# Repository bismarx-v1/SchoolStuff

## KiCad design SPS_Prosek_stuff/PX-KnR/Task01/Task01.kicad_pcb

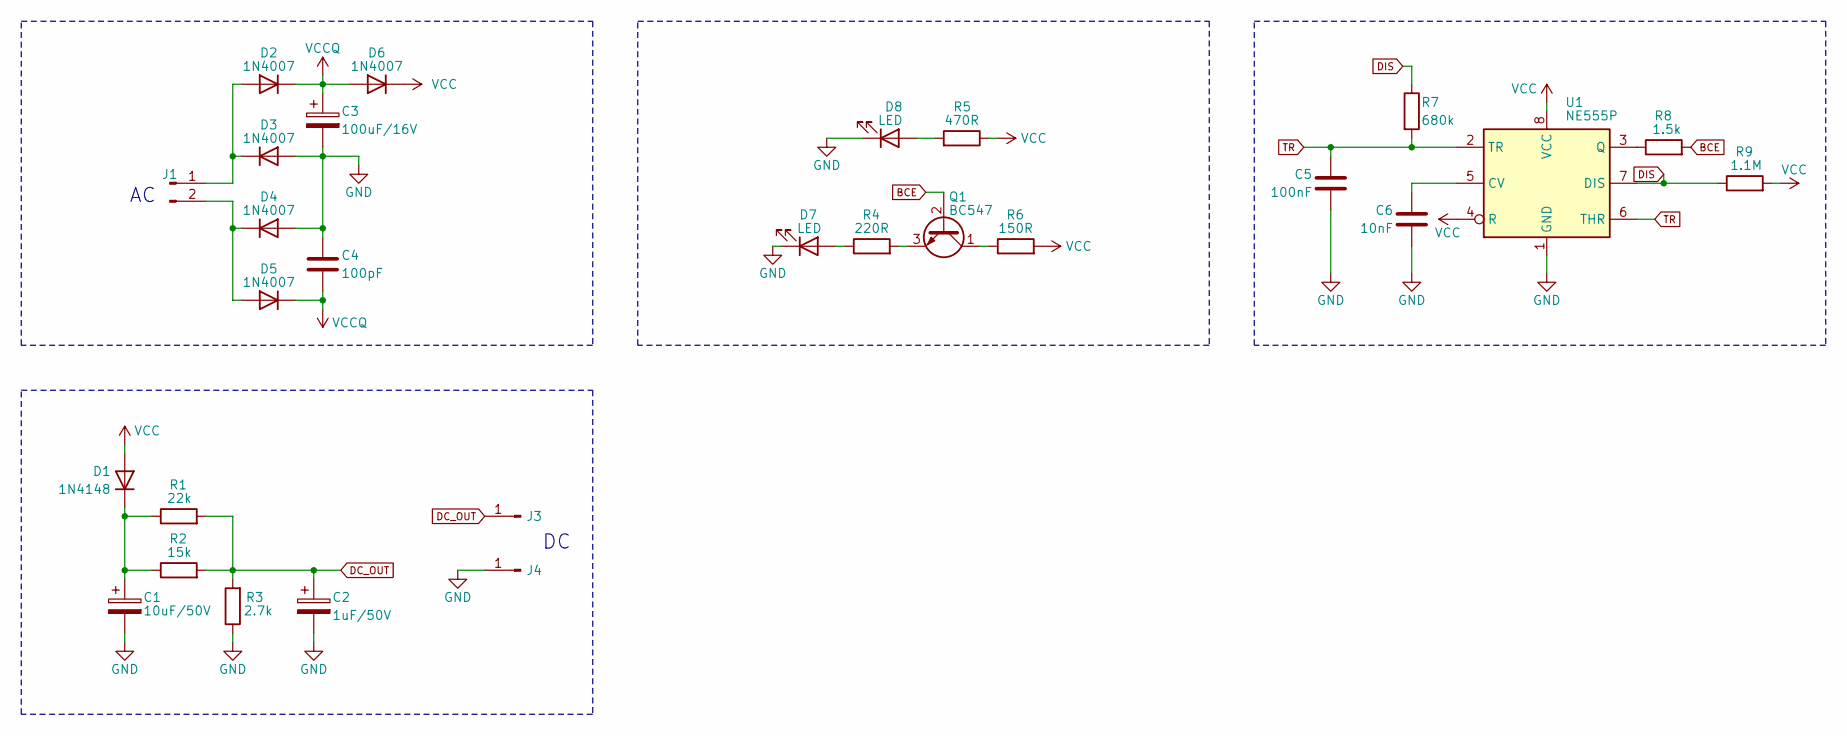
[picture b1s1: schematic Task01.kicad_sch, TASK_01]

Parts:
C1: 10uF/50V; CP_Radial_D6.3mm_P2.50mm
C2: 1uF/50V; CP_Radial_D6.3mm_P2.50mm
C3: 100uF/16V; CP_Radial_D6.3mm_P2.50mm
C4: 100pF; C_Disc_D6.0mm_W2.5mm_P5.00mm
C5: 100nF; C_Disc_D6.0mm_W2.5mm_P5.00mm
C6: 10nF; C_Disc_D6.0mm_W2.5mm_P5.00mm
D1: 1N4148; D_DO-35_SOD27_P7.62mm_Horizontal
D2, D3, D4, D5, D6: 1N4007; D_DO-41_SOD81_P10.16mm_Horizontal
D7, D8: LED; LED_D5.0mm_Clear
J1: Conn_01x02_Pin; PinHeader_1x02_P2.54mm_Vertical
J3, J4: DC; PinHeader_1x01_P2.54mm_Vertical
Q1: BC547; TO-92_Inline
R1: 22k; R_Axial_DIN0207_L6.3mm_D2.5mm_P10.16mm_Horizontal
R2: 15k; R_Axial_DIN0207_L6.3mm_D2.5mm_P10.16mm_Horizontal
R3: 2.7k; R_Axial_DIN0207_L6.3mm_D2.5mm_P10.16mm_Horizontal
R4: 220R; R_Axial_DIN0207_L6.3mm_D2.5mm_P10.16mm_Horizontal
R5: 470R; R_Axial_DIN0207_L6.3mm_D2.5mm_P10.16mm_Horizontal
R6: 150R; R_Axial_DIN0207_L6.3mm_D2.5mm_P10.16mm_Horizontal
R7: 680k; R_Axial_DIN0207_L6.3mm_D2.5mm_P10.16mm_Horizontal
R8: 1.5k; R_Axial_DIN0207_L6.3mm_D2.5mm_P10.16mm_Horizontal
R9: 1.1M; R_Axial_DIN0207_L6.3mm_D2.5mm_P10.16mm_Horizontal
U1: NE555P; DIP-8_W7.62mm

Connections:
BCE: Q1.2 (B), R8.2
DC_OUT: C2.1, J3.1, R1.2, R2.2, R3.2
DIS: R7.1, R9.1, U1.7 (DIS)
GND: C1.2, C2.2, C3.2, C4.1, C5.2, C6.2, D3.2 (A), D4.2 (A), D7.1 (K), D8.1 (K), J4.1, R3.1, U1.1 (GND)
unnamed: C1.1, D1.1 (K), R1.1, R2.1
unnamed: D2.2 (A), D3.1 (K), J1.1
unnamed: D4.1 (K), D5.2 (A), J1.2
unnamed: D7.2 (A), R4.1
unnamed: D8.2 (A), R5.2
unnamed: Q1.1 (C), R6.1
unnamed: Q1.3 (E), R4.2
unnamed: C6.1, U1.5 (CV)
unnamed: R8.1, U1.3 (Q)
TR: C5.1, R7.2, U1.2 (TR), U1.6 (THR)
VCC: D1.2 (A), D6.1 (K), R5.1, R6.2, R9.2, U1.4 (R), U1.8 (VCC)
VCCQ: C3.1, C4.2, D2.1 (K), D5.1 (K), D6.2 (A)

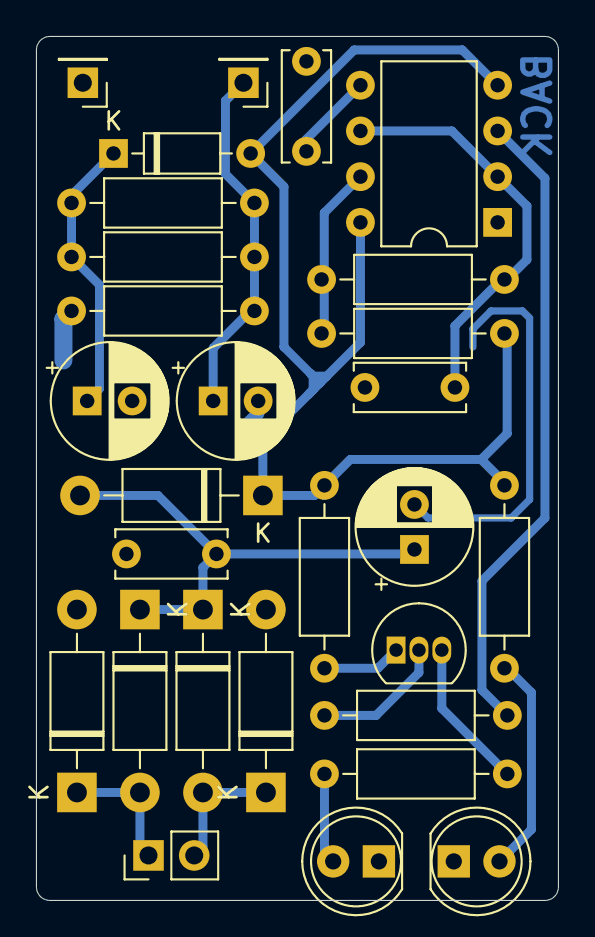
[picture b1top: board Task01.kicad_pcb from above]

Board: 2 copper layers, 29.0 x 48.0 mm, 28 parts (0 on the bottom side), 16 nets.

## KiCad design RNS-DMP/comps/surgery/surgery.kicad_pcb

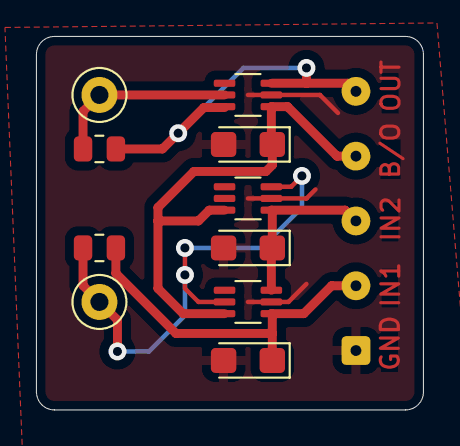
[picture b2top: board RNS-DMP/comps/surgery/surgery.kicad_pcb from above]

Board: 2 copper layers, 21.5 x 20.8 mm, 11 parts (0 on the bottom side), 7 nets.

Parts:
C2, C3, C4: 1uF; CP_EIA-3216-18_Kemet-A
J1: Conn_01x05_Pin; SolderWire-0.1sqmm_1x05_P3.6mm_D0.4mm_OD1mm
R4, R6: 10k; R_0805_2012Metric
TP1, TP2: TestPoint; TestPoint_Loop_D1.80mm_Drill1.0mm_Beaded
U2, U3, U4: LM66100Q; SOT-363_SC-70-6_wide

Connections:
BRWN: C4.1, J1.4, U2.6 (VOUT), U3.6 (VOUT), U4.1 (VIN)
GND: C2.2, C3.2, C4.2, J1.1, U2.2 (GND), U3.2 (GND), U4.2 (GND)
unnamed: R4.2, TP1.1, U2.5 (ST), U3.3 (~CE)
unnamed: R6.2, TP2.1, U4.5 (ST)
SRC_5V: C2.1, J1.2, R4.1, U2.1 (VIN)
SUPERCAP: J1.5, R6.1, U4.3 (~CE), U4.6 (VOUT)
VBUS: C3.1, J1.3, U2.3 (~CE), U3.1 (VIN)

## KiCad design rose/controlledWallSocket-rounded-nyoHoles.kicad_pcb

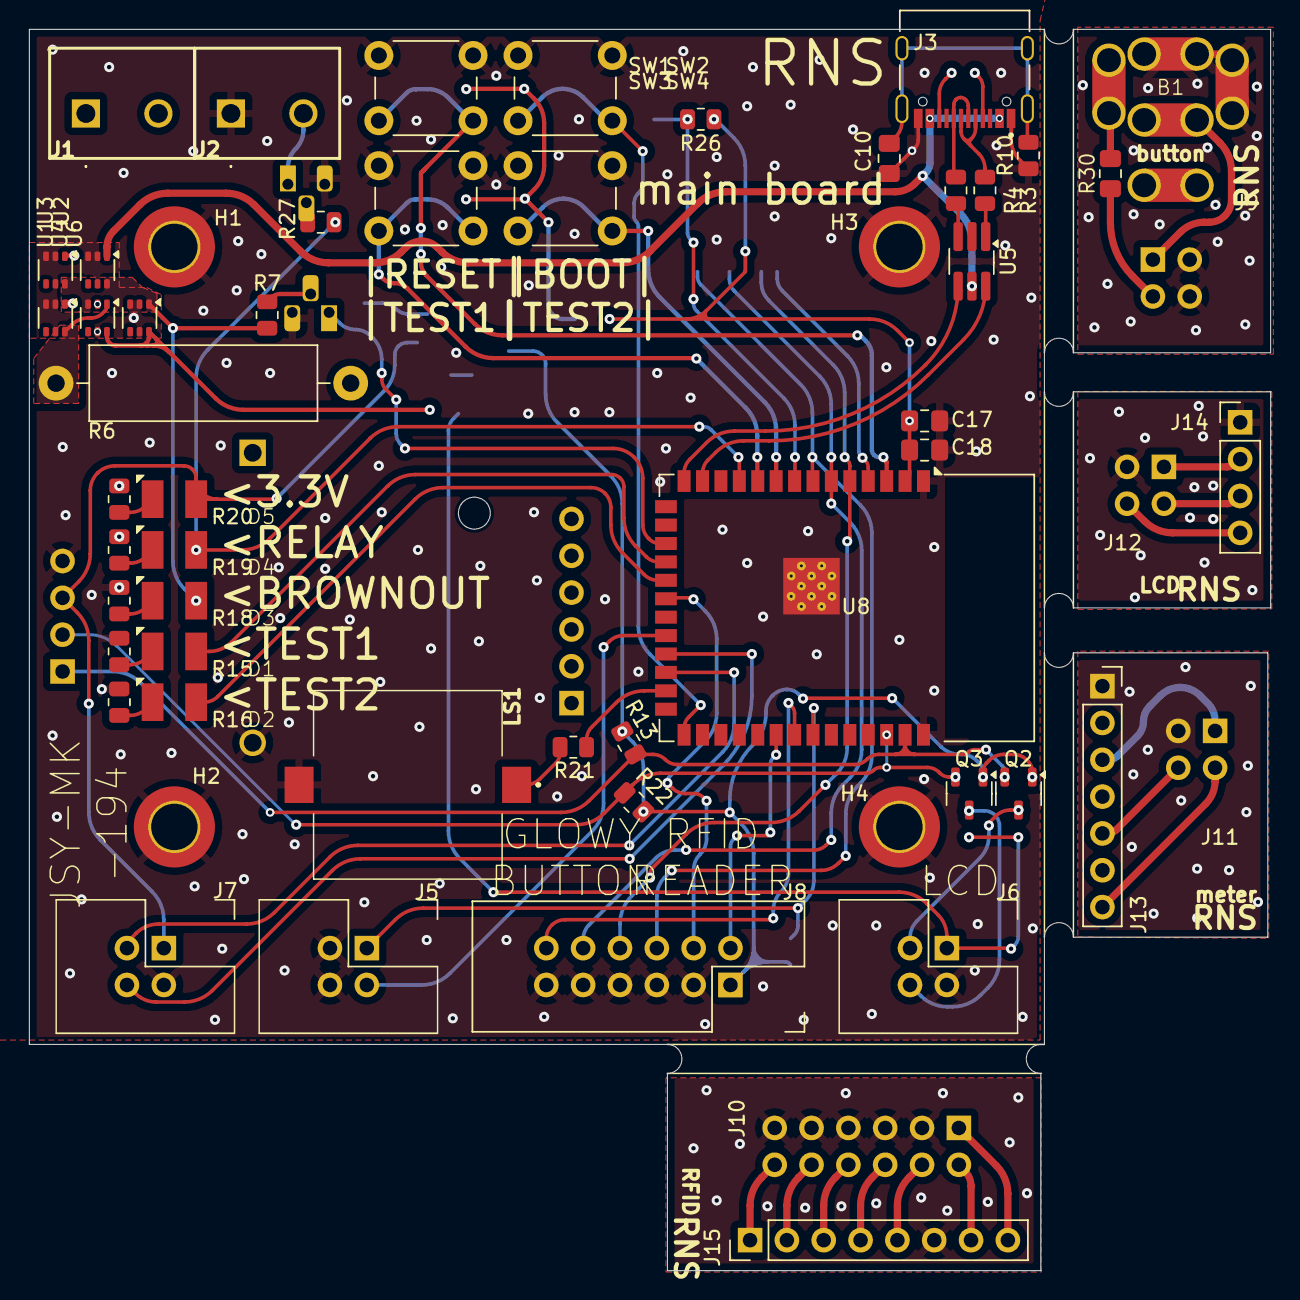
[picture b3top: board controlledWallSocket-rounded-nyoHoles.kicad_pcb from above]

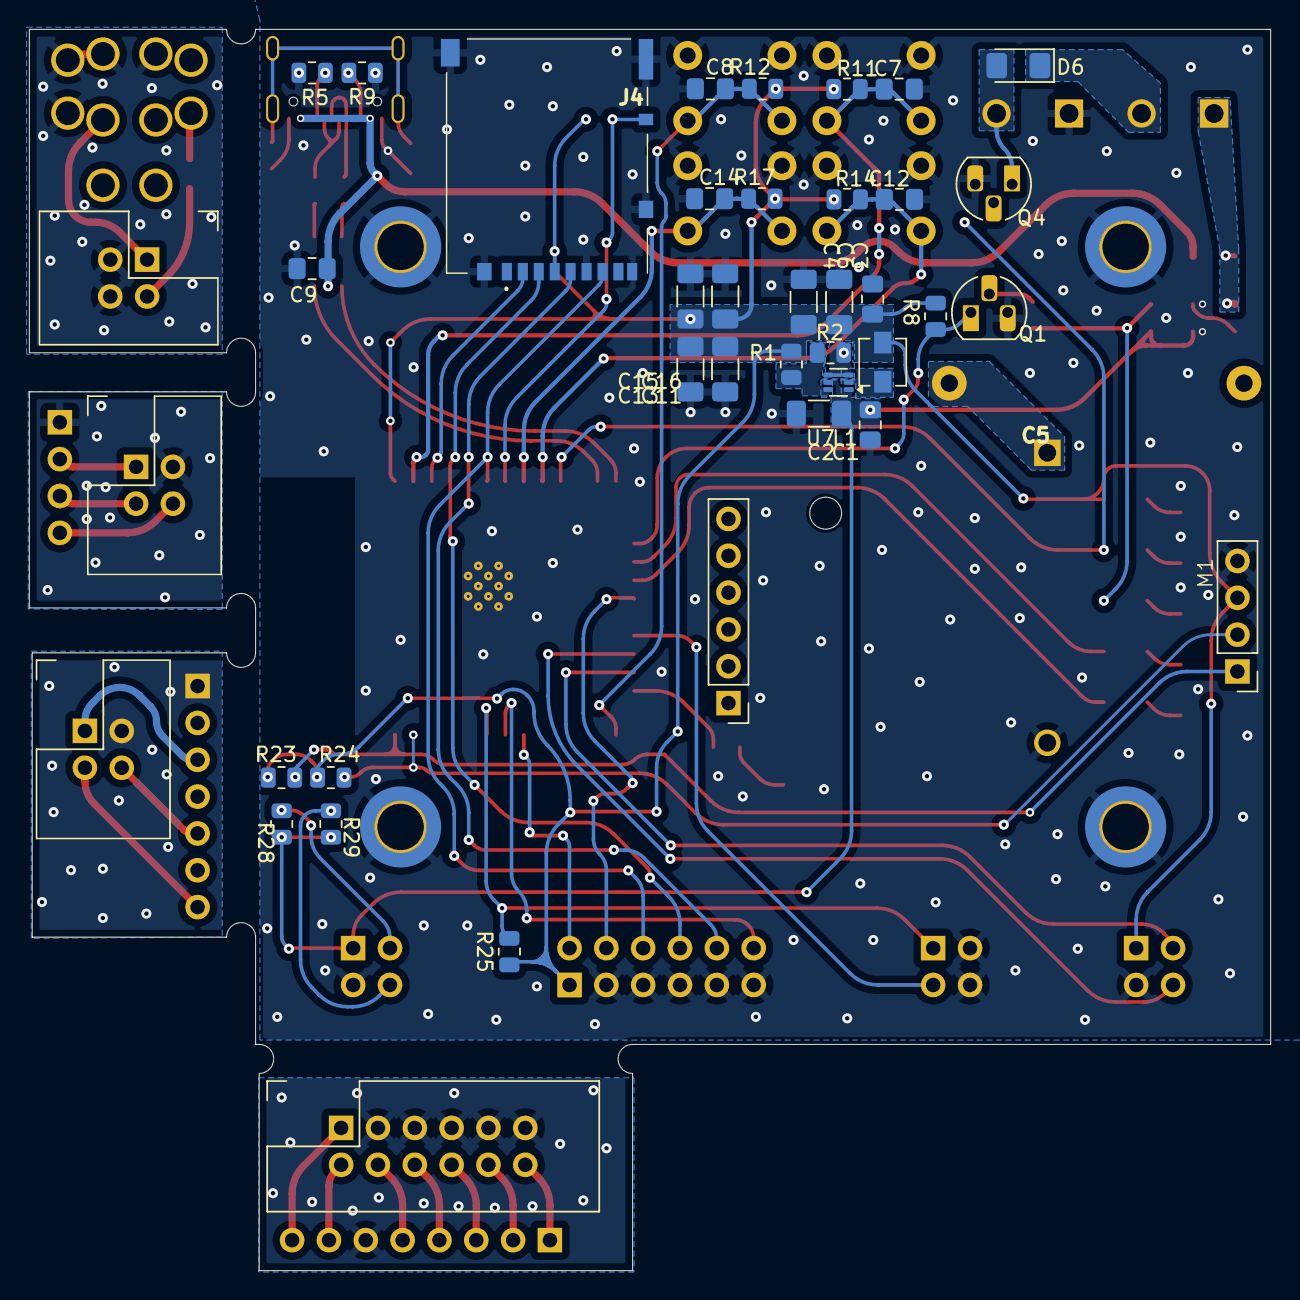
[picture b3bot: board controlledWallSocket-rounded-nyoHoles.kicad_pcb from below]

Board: 2 copper layers, 85.6 x 85.6 mm, 93 parts (40 on the bottom side), 74 nets.

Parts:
B1: Button; button
C1, C3, C7, C8, C9, C10, C12, C14, C18: 100nF; C_0805_2012Metric_Pad1.18x1.45mm_HandSolder
C2, C4, C6: 22u; C_1206_3216Metric_Pad1.33x1.80mm_HandSolder
C5: supercapacitor_KVR-5R0H105-R; supercapacitor_KVR5R0H105R
C11, C13, C15, C16: #; C_1206_3216Metric_Pad1.33x1.80mm_HandSolder
C17: 10uF; C_0805_2012Metric_Pad1.18x1.45mm_HandSolder
D1: pink; led3528
D2: violet; led3528
D3: blue; led3528
D4: green; led3528
D5: yellow; led3528
D6: SD1206S040S2R0; D_1206_3216Metric_Pad1.42x1.75mm_HandSolder
H1, H2, H3, H4: M3; MountingHole_3.2mm_M3_DIN965_Pad_TopBottom
J1, J2: screw term. 2x1 5mm; screwTerminal_DG3015002P1200AH
J3: USB_TypeC; usbC_HRO_TYPE-C-31-M-12
J4: sdCard_DM3AT-SF-PEJM5; sdCard_DM3ATSFPEJM5
J5, J6, J7, J9, J11, J12: IDC 2x2; IDC 2x2 2.54
J8, J10: IDC 6x2; IDC 6x2 2.54
J13: pinHeader 7x1 2.54mm; PinSocket_1x07_P2.54mm_Vertical
J14: pinHeader 4x1 2.54mm; PinHeader_1x04_P2.54mm_Vertical
J15: Conn_01x08_Pin; PinHeader_1x08_P2.54mm_Vertical
L1: 1.5u; L_Vishay_IHLP-1212
LS1: buzzer_CPT-1625-80-SMT-TR; buzzer_CPT162580SMTTR
M1: RTC and EEPROM
Q1, Q4: bc337; TO-92_HandSolder
Q2, Q3: BSS138; SOT-23-3
R1: 45k; R_0805_2012Metric
R2, R8, R11, R12, R13, R14, R17, R22, R23, R24, R25, R26, R28, R29: 10k; R_0805_2012Metric
R3, R4: 15R; R_0805_2012Metric
R5, R9: 5.1k; R_0805_2012Metric
R6: 4.7R; R_Axial_DIN0516_L15.5mm_D5.0mm_P20.32mm_Horizontal
R7, R18, R27: 1k; R_0805_2012Metric
R10: 100k; R_0805_2012Metric
R15, R16, R19, R20: 220R; R_0805_2012Metric
R21: 0R; R_0805_2012Metric
R30: 100R; C_0805_2012Metric_Pad1.18x1.45mm_HandSolder
SW1, SW2, SW3, SW4: SW_Push; SW_PUSH_6mm_H13mm
U1, U2, U3, U4, U6: LM66100Q; SOT-363_SC-70-6
U5: USBLC6-2SC6; TSOT-23-6_HandSoldering
U7: TPS565242DRLR; SOT-563
U8: ESP32-S3-WROOM-1

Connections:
+3.3V: C3.1, C4.1, C6.1, C11.1, C13.1, C15.1, C16.1, C17.1, C18.1, D5.2 (A), J4.4 (VDD), J7.1, J8.1, L1.2, M1.3 (VCC), Q2.1 (G), Q3.1 (G), R1.2, R8.1, R11.2, R12.2, R13.1, R14.2, R17.2, R22.1, R23.2, R24.2, R25.1, R26.1, U8.2 (3V3)
+5V: C1.1, C2.1, J6.1, R28.2, R29.2, U4.6 (VOUT), U6.6 (VOUT), U7.1 (VIN), U7.5 (EN)
+24V: D6.1 (K), J1.2
ESP_EN-btn_rst: C7.2, R11.1, SW1.2, U8.3 (EN)
ESP_IO0_BOOT-btn_boot: C8.2, R12.1, SW2.2, U8.27 (IO0)
ESP_IO04-btn_test1: C12.2, R14.1, SW3.2, U8.10 (IO17)
ESP_IO05-btn_test2: C14.2, R17.1, SW4.2, U8.9 (IO16)
ESP_IO6-RFID_IRQ: J8.4, U8.20 (IO12)
ESP_IO7-RFID_NRSTPD: J8.2, U8.32 (IO39)
ESP_IO8-SPI_CS_rfid: J8.12, U8.33 (IO40)
ESP_IO9-SPI_CS_sdCard: J4.2 (CD/DAT3), U8.4 (IO4)
ESP_IO10-SPI_MOSI: J4.3 (CMD), J8.8, U8.5 (IO5)
ESP_IO11-SPI_MISO: J4.7 (DAT0), J8.6, U8.7 (IO7)
ESP_IO12-SPI_CLK: J4.5 (CLK), J8.10, U8.6 (IO6)
ESP_IO13-UART_espRx: J7.2, U8.24 (IO47)
ESP_IO14-UART_espTx: J7.4, U8.23 (IO21)
ESP_IO15-IIC_SDA: M1.1 (SCL), Q2.2 (S), R13.2, R23.1, U8.39 (IO1)
ESP_IO16-IIC_SCL: M1.2 (SDA), Q3.2 (S), R22.2, R24.1, U8.38 (IO2)
ESP_IO38-relay_control: D4.2 (A), R27.1, U8.11 (IO18)
ESP_IO39-brownout_detected: Q1.1 (C), R8.2, U8.17 (IO9)
ESP_IO40-btnGlow_button: J5.1, R25.2, U8.34 (IO41)
ESP_IO41-btnGlow_LED: J5.3, U8.22 (IO14)
ESP_IO42-sdCardPresent: J4.MP4, R26.2, U8.8 (IO15)
ESP_IO47-led_test1: D1.2 (A), U8.18 (IO10)
ESP_IO48-led_test2: D2.2 (A), U8.19 (IO11)
ESP_IO#-buzzer: R21.2, U8.25 (IO48)
ESP_USB_D#-USB_MAIN_DN: U5.6, U8.13 (USB_D-)
ESP_USB_D#-USB_MAIN_DP: U5.4, U8.14 (USB_D+)
GND: C1.2, C2.2, C3.2, C4.2, C5.2 (-), C6.2, C7.1, C8.1, C9.2, C10.1, C11.2, C12.1, C13.2, C14.1, C15.2, C16.2, C17.2, C18.2, H1.1, H2.1, H3.1, H4.1, J2.1, J3.A1_B12 (GND), J3.B1_A12 (GND), J4.6 (VSS), J4.MP1, J4.MP2, J4.MP3, J4.MP5, J4.MP6, J5.2, J5.4, J6.3, J7.3, J8.3, J8.5, J8.7, J8.9, J8.11, LS1.2 (-), M1.4 (VSS), Q1.3 (E), Q4.3 (E), R2.1, R5.1, R9.1, R10.2, R15.2, R16.2, R18.2, R19.2, R20.2, SW1.1, SW2.1, SW3.1, SW4.1, U1.2 (GND), U1.3 (~CE), U1.5 (ST), U2.2 (GND), U2.3 (~CE), U2.5 (ST), U3.2 (GND), U3.3 (~CE), U3.5 (ST), U4.2 (GND), U4.5 (ST), U5.2, U6.2 (GND), U6.3 (~CE), U6.5 (ST), U7.3 (GND), U7.4 (AGND), U8.1 (GND), U8.40 (GND), U8.41 (GND)
IIC_5V_SDA: J6.2, Q2.3 (D), R28.1
IIC_5V_SLC: J6.4, Q3.3 (D), R29.1
unnamed: B1.5 (LP), R30.1
unnamed: C5.1 (+), R6.1
unnamed: C10.2, J3.S1 (SHIELD), J3.S2 (SHIELD), J3.S3 (SHIELD), J3.S4 (SHIELD), R10.1
unnamed: D1.1 (K), R15.1
unnamed: D2.1 (K), R16.1
unnamed: D3.1 (K), R18.1
unnamed: D4.1 (K), R19.1
unnamed: D5.1 (K), R20.1
unnamed: J3.A5 (CC1), R5.2
unnamed: J3.B5 (CC2), R9.2
unnamed: J10.1, J15.8
unnamed: J10.2, J15.7
unnamed: J10.4, J15.5
unnamed: J10.6, J15.4
unnamed: J10.8, J15.3
unnamed: J10.10, J15.2
unnamed: J10.3, J10.5, J10.7, J10.9, J10.11, J15.6
unnamed: J10.12, J15.1
unnamed: J11.1, J13.3
unnamed: J11.2, J13.7
unnamed: J11.3, J13.1
unnamed: J11.4, J13.5
unnamed: J12.1, J14.2
unnamed: J12.2, J14.3
unnamed: J12.3, J14.1
unnamed: J12.4, J14.4
unnamed: LS1.1 (+), R21.1
unnamed: Q1.2 (B), R7.2
unnamed: Q4.2 (B), R27.2
unnamed: R3.2, U5.1
unnamed: R4.2, U5.3
unnamed: R6.2, U1.6 (VOUT), U4.1 (VIN)
unnamed: R1.1, R2.2, U7.6 (FB)
unnamed: L1.1, U7.2 (SW)
USB_MAIN_DN: J3.A7 (DN1), J3.B7 (DN2), R3.1
USB_MAIN_DP: J3.A6 (DP1), J3.B6 (DP2), R4.1
USB_MAIN_Vbus: C9.1, J3.A4_B9 (VBUS), J3.B4_A9 (VBUS), U2.1 (VIN), U5.5
bG_GND: B1.1 (Com), B1.4 (LN), J9.2, J9.4
bG_LED: J9.3, R30.2
bG_button: B1.2 (NO), J9.1
raw_5V: J1.1, U1.1 (VIN), U3.1 (VIN)
relay_control: D6.2 (A), J2.2, Q4.1 (C)
statusLed_brownout_5V: D3.2 (A), R7.1, U2.6 (VOUT), U3.6 (VOUT), U4.3 (~CE), U6.1 (VIN)

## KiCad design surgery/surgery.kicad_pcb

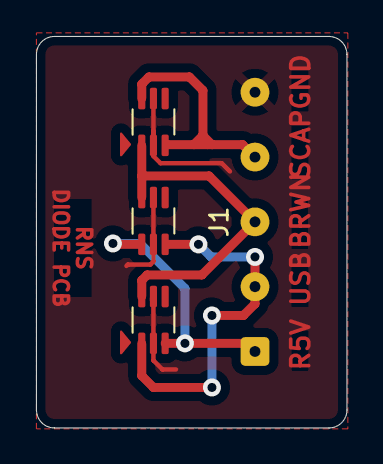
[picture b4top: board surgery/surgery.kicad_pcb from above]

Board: 2 copper layers, 17.2 x 21.8 mm, 4 parts (0 on the bottom side), 5 nets.

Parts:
J1: Conn_01x05_Pin; SolderWire-0.1sqmm_1x05_P3.6mm_D0.4mm_OD1mm
U2, U3, U4: LM66100Q; SOT-363_SC-70-6_wide

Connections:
GND: J1.5, U2.2 (GND), U2.5 (ST), U3.2 (GND), U3.5 (ST), U4.2 (GND), U4.5 (ST)
USB_MAIN_Vbus: J1.2, U2.3 (~CE), U3.1 (VIN)
brown-out: J1.3, U2.6 (VOUT), U3.6 (VOUT), U4.1 (VIN)
raw_5V: J1.1, U2.1 (VIN), U3.3 (~CE)
supercap: J1.4, U4.3 (~CE), U4.6 (VOUT)

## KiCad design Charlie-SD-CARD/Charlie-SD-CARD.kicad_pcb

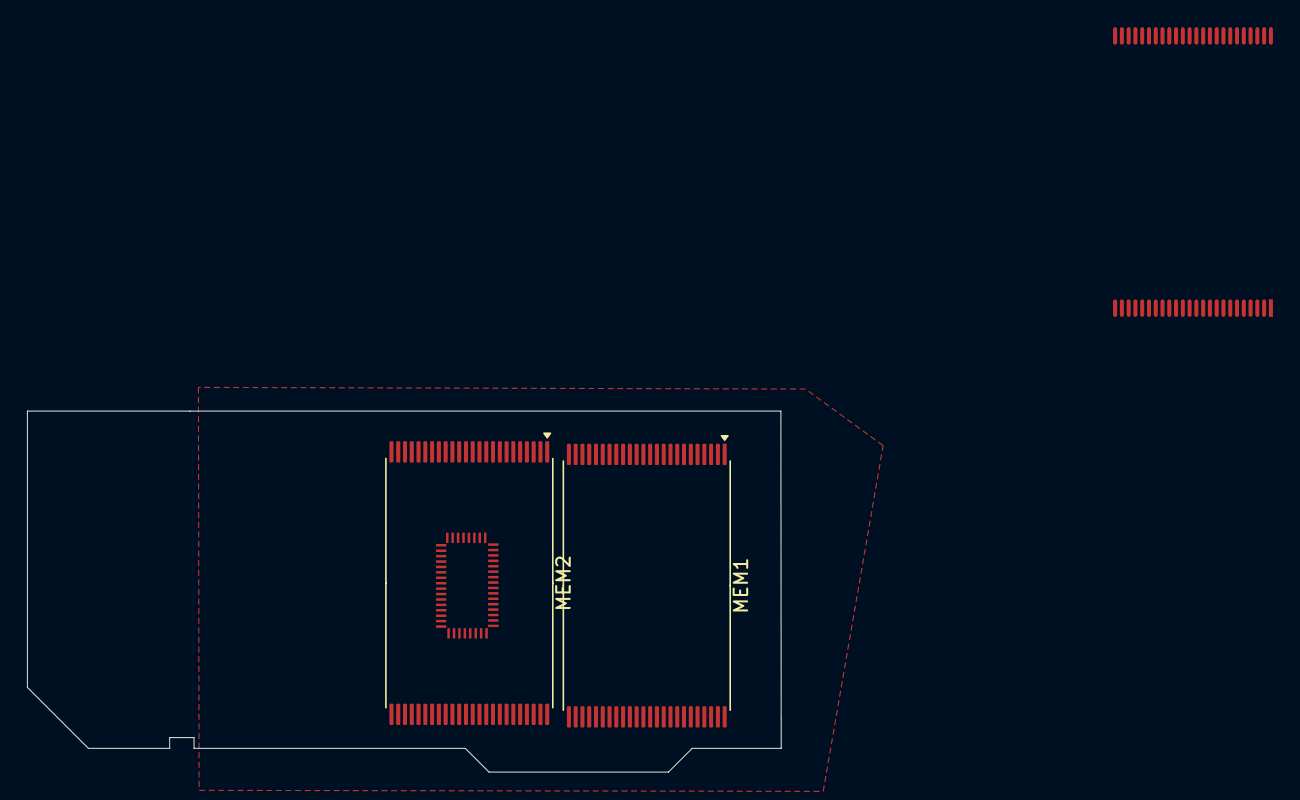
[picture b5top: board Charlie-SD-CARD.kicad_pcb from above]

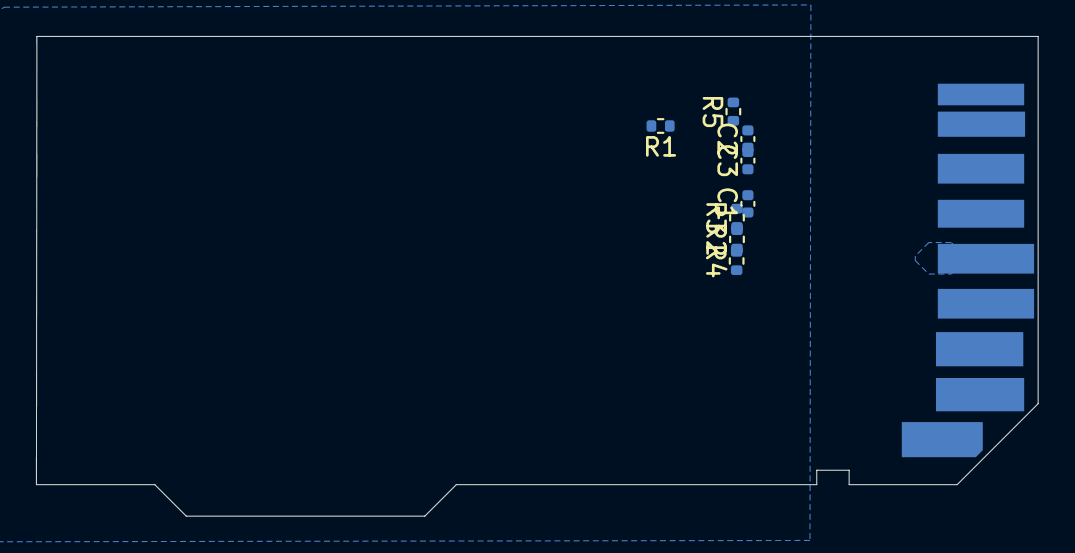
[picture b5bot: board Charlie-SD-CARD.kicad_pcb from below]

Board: 2 copper layers, 55.7 x 26.6 mm, 13 parts (9 on the bottom side), 42 nets, no tracks yet.

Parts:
C1, C2, C3: C; C_0402_1005Metric
MC1: mc
MEM1, MEM2: TSOP-I-48_18.4x12mm_P0.5mm
MEM1#2: memory
R1: 32~35R; R_0402_1005Metric
R2: >~1000R; R_0402_1005Metric
R3: ~1000R; R_0402_1005Metric
R4: ~15R; R_0402_1005Metric
R5: ?R; R_0402_1005Metric
SD1: sdCard

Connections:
CLK/SCLK: R1.1, SD1.6
CMD/DI: MC1.35, SD1.3
DAT0/DO: MC1.48, SD1.8
DAT1/X: C2.1, C3.1, MC1.43, MC1.44, MEM1.12, MEM1.37, MEM2.12, MEM2.37, R2.2, R3.2, SD1.5, SD1.9
DAT2/X: MC1.32, SD1.1
DAT3/CS: MC1.33, SD1.2
GND/GND: C1.2, C2.2, C3.2, MC1.37, MC1.38, MC1.39, MEM1.13, MEM1.36, MEM1.38, MEM2.13, MEM2.36, MEM2.38, R4.2, SD1.4, SD1.7
jmp1: MC1.45, R1.2
jmp2: MC1.4, MEM1.7, MEM2.7, R2.1
jmp3: MC1.3, R3.1
jmp4: MEM1.6, MEM2.6, R4.1
jmp5: MC1.1, R5.2
jmp6: MC1.42, R5.1
jmp7: C1.1, MC1.2
jmp8: MC1.5, MEM2.8
jmp9: MC1.6, MEM1.9, MEM2.9
jmp10: MC1.7, MEM1.10, MEM2.10
jmp11: MC1.8, MEM2.16
jmp12: MC1.9, MEM2.17
jmp13: MC1.10, MEM2.18
jmp14: MC1.11, MEM1.19, MEM2.19
jmp15: MC1.12, MEM1.8
jmp16: MC1.13, MEM1.16
jmp17: MC1.14, MEM1.17
jmp18: MC1.15, MEM1.18
jmp19: MC1.16, MEM1.29
jmp20: MC1.17, MEM1.30
jmp21: MC1.18, MEM1.31
jmp22: MC1.19, MEM1.32
jmp23: MC1.20, MEM1.41
jmp24: MC1.21, MEM1.42
jmp25: MC1.22, MEM1.43
jmp26: MC1.23, MEM1.44
jmp27: MC1.24, MEM2.29
jmp28: MC1.25, MEM2.30
jmp29: MC1.26, MEM2.31
jmp30: MC1.27, MEM2.32
jmp31: MC1.28, MEM2.41
jmp32: MC1.29, MEM2.42
jmp33: MC1.30, MEM2.43
jmp34: MC1.31, MEM2.44
jmp35: MEM1.1, MEM2.1

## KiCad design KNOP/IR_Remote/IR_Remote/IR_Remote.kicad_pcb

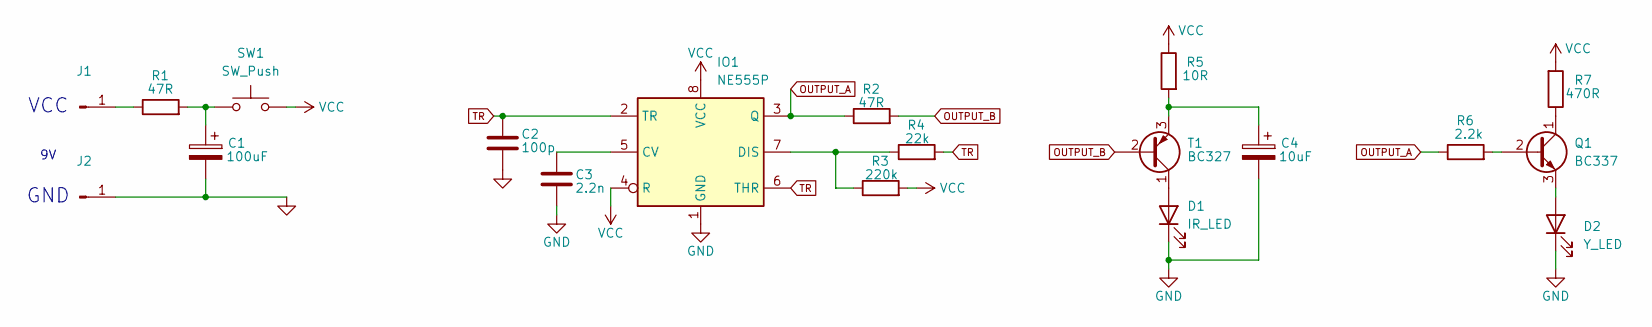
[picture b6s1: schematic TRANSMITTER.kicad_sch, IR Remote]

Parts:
C1: 100uF; CP_Radial_D6.3mm_P2.50mm
C2: 100p
C3: 2.2n
C4: 10uF; CP_EIA-3216-18_Kemet-A_Pad1.58x1.35mm_HandSolder
D1: IR_LED
D2: Y_LED
IO1: NE555P; DIP-8_W7.62mm
J1, J2: Conn_01x01_Pin
Q1: BC337; TO-92_Inline
R1, R2: 47R; R_0805_2012Metric_Pad1.20x1.40mm_HandSolder
R3: 220k; R_0805_2012Metric_Pad1.20x1.40mm_HandSolder
R4: 22k; R_0805_2012Metric_Pad1.20x1.40mm_HandSolder
R5: 10R; R_0805_2012Metric_Pad1.20x1.40mm_HandSolder
R6: 2.2k; R_0805_2012Metric_Pad1.20x1.40mm_HandSolder
R7: 470R; R_0805_2012Metric_Pad1.20x1.40mm_HandSolder
SW1: SW_Push; SW_PUSH_6mm_H5mm
T1: BC327; TO-92_Inline

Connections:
GND: C1.2, C2.1, C3.2, C4.2, D1.1 (K), D2.1 (K), IO1.1 (GND), J2.1; also elsewhere on the board
unnamed: C1.1, R1.2, SW1.1
unnamed: D1.2 (A), T1.1 (C)
unnamed 7: D2.2 (A), Q1.3 (E); also elsewhere on the board
unnamed: C3.1, IO1.5 (CV)
unnamed: IO1.7 (DIS), R3.1, R4.1
unnamed: J1.1, R1.1
unnamed: C4.1, R5.2, T1.3 (E)
unnamed 18: Q1.2 (B), R6.2; also elsewhere on the board
unnamed 19: Q1.1 (C), R7.1; also elsewhere on the board
OUTPUT_A: IO1.3 (Q), R2.1, R6.1
OUTPUT_B: R2.2, T1.2 (B)
TR: C2.2, IO1.2 (TR), IO1.6 (THR), R4.2
VCC: IO1.4 (R), IO1.8 (VCC), R3.2, R5.1, R7.2, SW1.2

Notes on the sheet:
GND
VCC

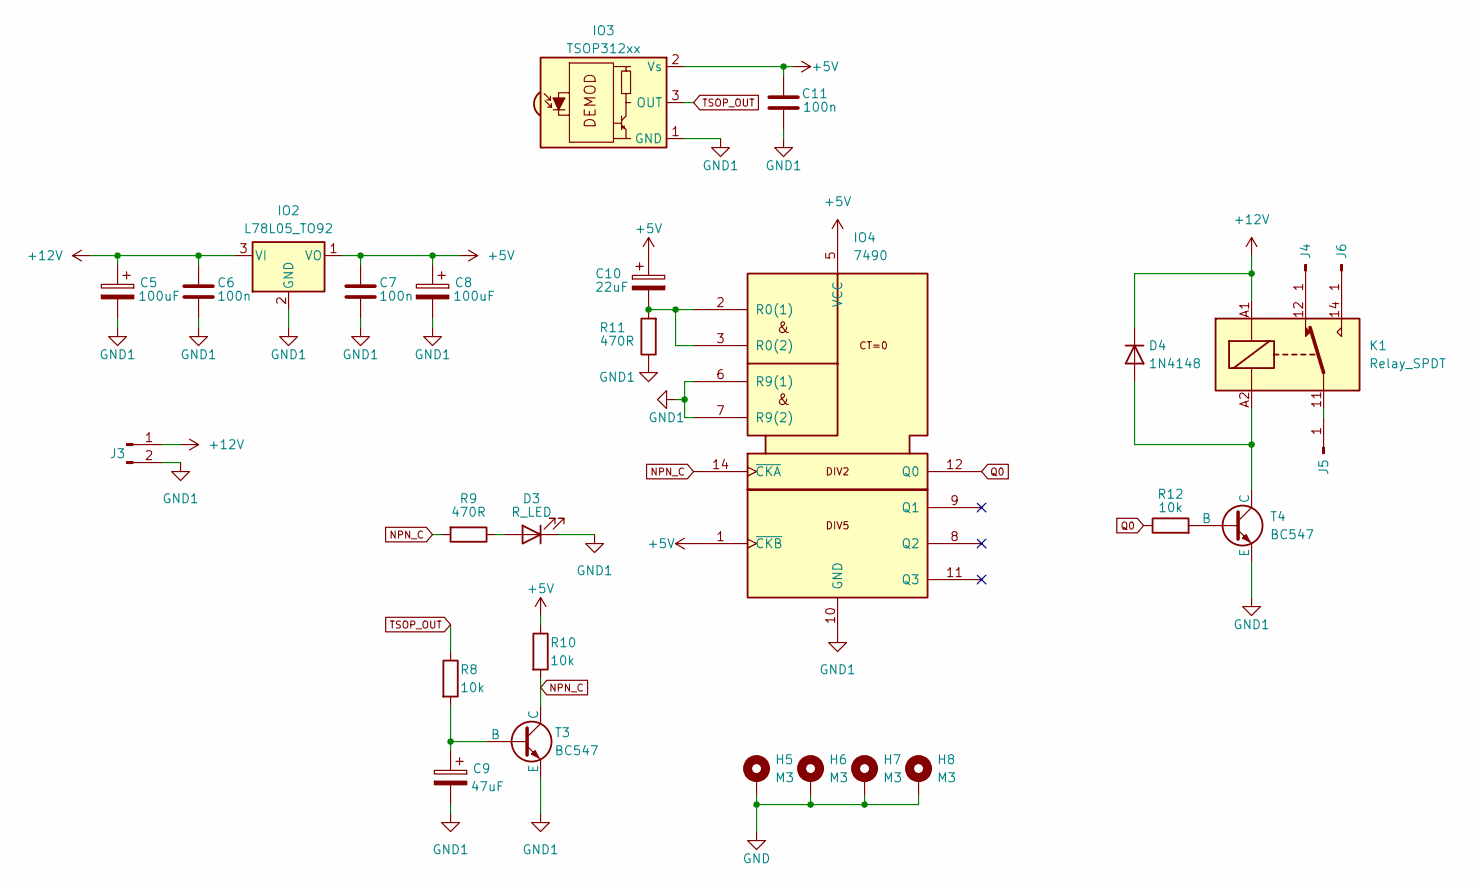
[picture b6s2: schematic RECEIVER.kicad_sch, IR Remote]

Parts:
C5, C8: 100uF; CP_Radial_D6.3mm_P2.50mm
C6, C7, C11: 100n; C_Disc_D7.5mm_W5.0mm_P10.00mm
C9: 47uF; CP_Radial_D6.3mm_P2.50mm
C10: 22uF; CP_Radial_D6.3mm_P2.50mm
D3: R_LED; LED_D5.0mm
D4: 1N4148; D_DO-35_SOD27_P7.62mm_Horizontal
H5, H6, H7, H8: M3; MountingHole_3.2mm_M3_ISO7380_Pad
IO2: L78L05_TO92; TO-92_Inline_Wide
IO3: TSOP312xx; Vishay_CAST-3Pin
IO4: 7490; DIP-14_W7.62mm
J3: Conn_01x02_Pin; PinHeader_1x02_P2.54mm_Vertical
J4, J5, J6: Conn_01x01_Pin; PinHeader_1x01_P2.54mm_Vertical
K1: Relay_SPDT; Relay_SPDT_Finder_36.11
R8, R10, R12: 10k; R_Axial_DIN0207_L6.3mm_D2.5mm_P10.16mm_Horizontal
R9, R11: 470R; R_Axial_DIN0207_L6.3mm_D2.5mm_P10.16mm_Horizontal
T3, T4: BC547; TO-92_Inline_Wide

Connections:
+5V: C7.2, C8.1, C10.1, C11.1, IO2.1 (VO), IO3.2 (Vs), IO4.1 (~CKB), IO4.5 (VCC), R10.1
+12V: C5.1, C6.2, D4.1 (K), IO2.3 (VI), J3.1, K1.A1
GND: H5.1, H6.1, H7.1, H8.1; also elsewhere on the board
GND1: C5.2, C6.1, C7.1, C8.2, C9.2, C11.2, D3.1 (K), IO2.2 (GND), IO3.1 (GND), IO4.6 (R9(1)), IO4.7 (R9(2)), IO4.10 (GND), J3.2, R11.1, T3.3 (E), T4.3 (E); also elsewhere on the board
NPN_C: IO4.14 (~CKA), R9.2, R10.2, T3.1 (C)
unnamed: D3.2 (A), R9.1
unnamed: D4.2 (A), K1.A2, T4.1 (C)
unnamed: C10.2, IO4.2 (R0(1)), IO4.3 (R0(2)), R11.2
unnamed: J4.1, K1.12
unnamed: J5.1, K1.11
unnamed: J6.1, K1.14
unnamed: C9.1, R8.2, T3.2 (B)
unnamed: R12.2, T4.2 (B)
Q0: IO4.12 (Q0), R12.1
TSOP_OUT: IO3.3 (OUT), R8.1

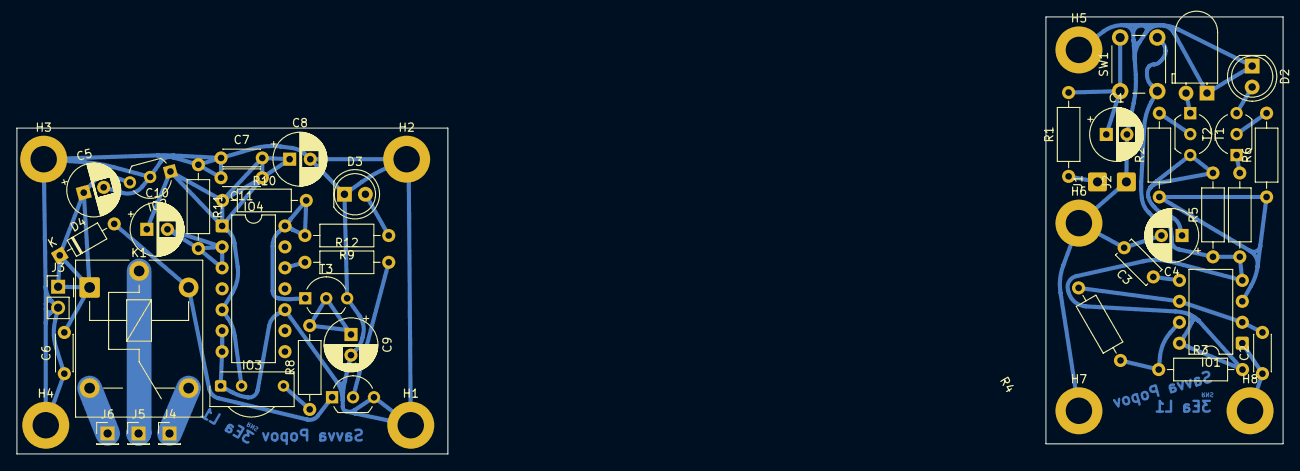
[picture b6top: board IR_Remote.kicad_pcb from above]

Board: 2 copper layers, 153.5 x 53.0 mm, 51 parts (0 on the bottom side), 28 nets.

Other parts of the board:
H1, H2, H3, H4: M3; MountingHole_3.2mm_M3_ISO7380_Pad
T2: BC337; TO-92_Inline_Wide

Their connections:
GND1: H1.1, H2.1, H3.1, H4.1; also elsewhere on the board
unnamed 7: T2.3 (E); also elsewhere on the board
unnamed 18: T2.2 (B); also elsewhere on the board
unnamed 19: T2.1 (C); also elsewhere on the board

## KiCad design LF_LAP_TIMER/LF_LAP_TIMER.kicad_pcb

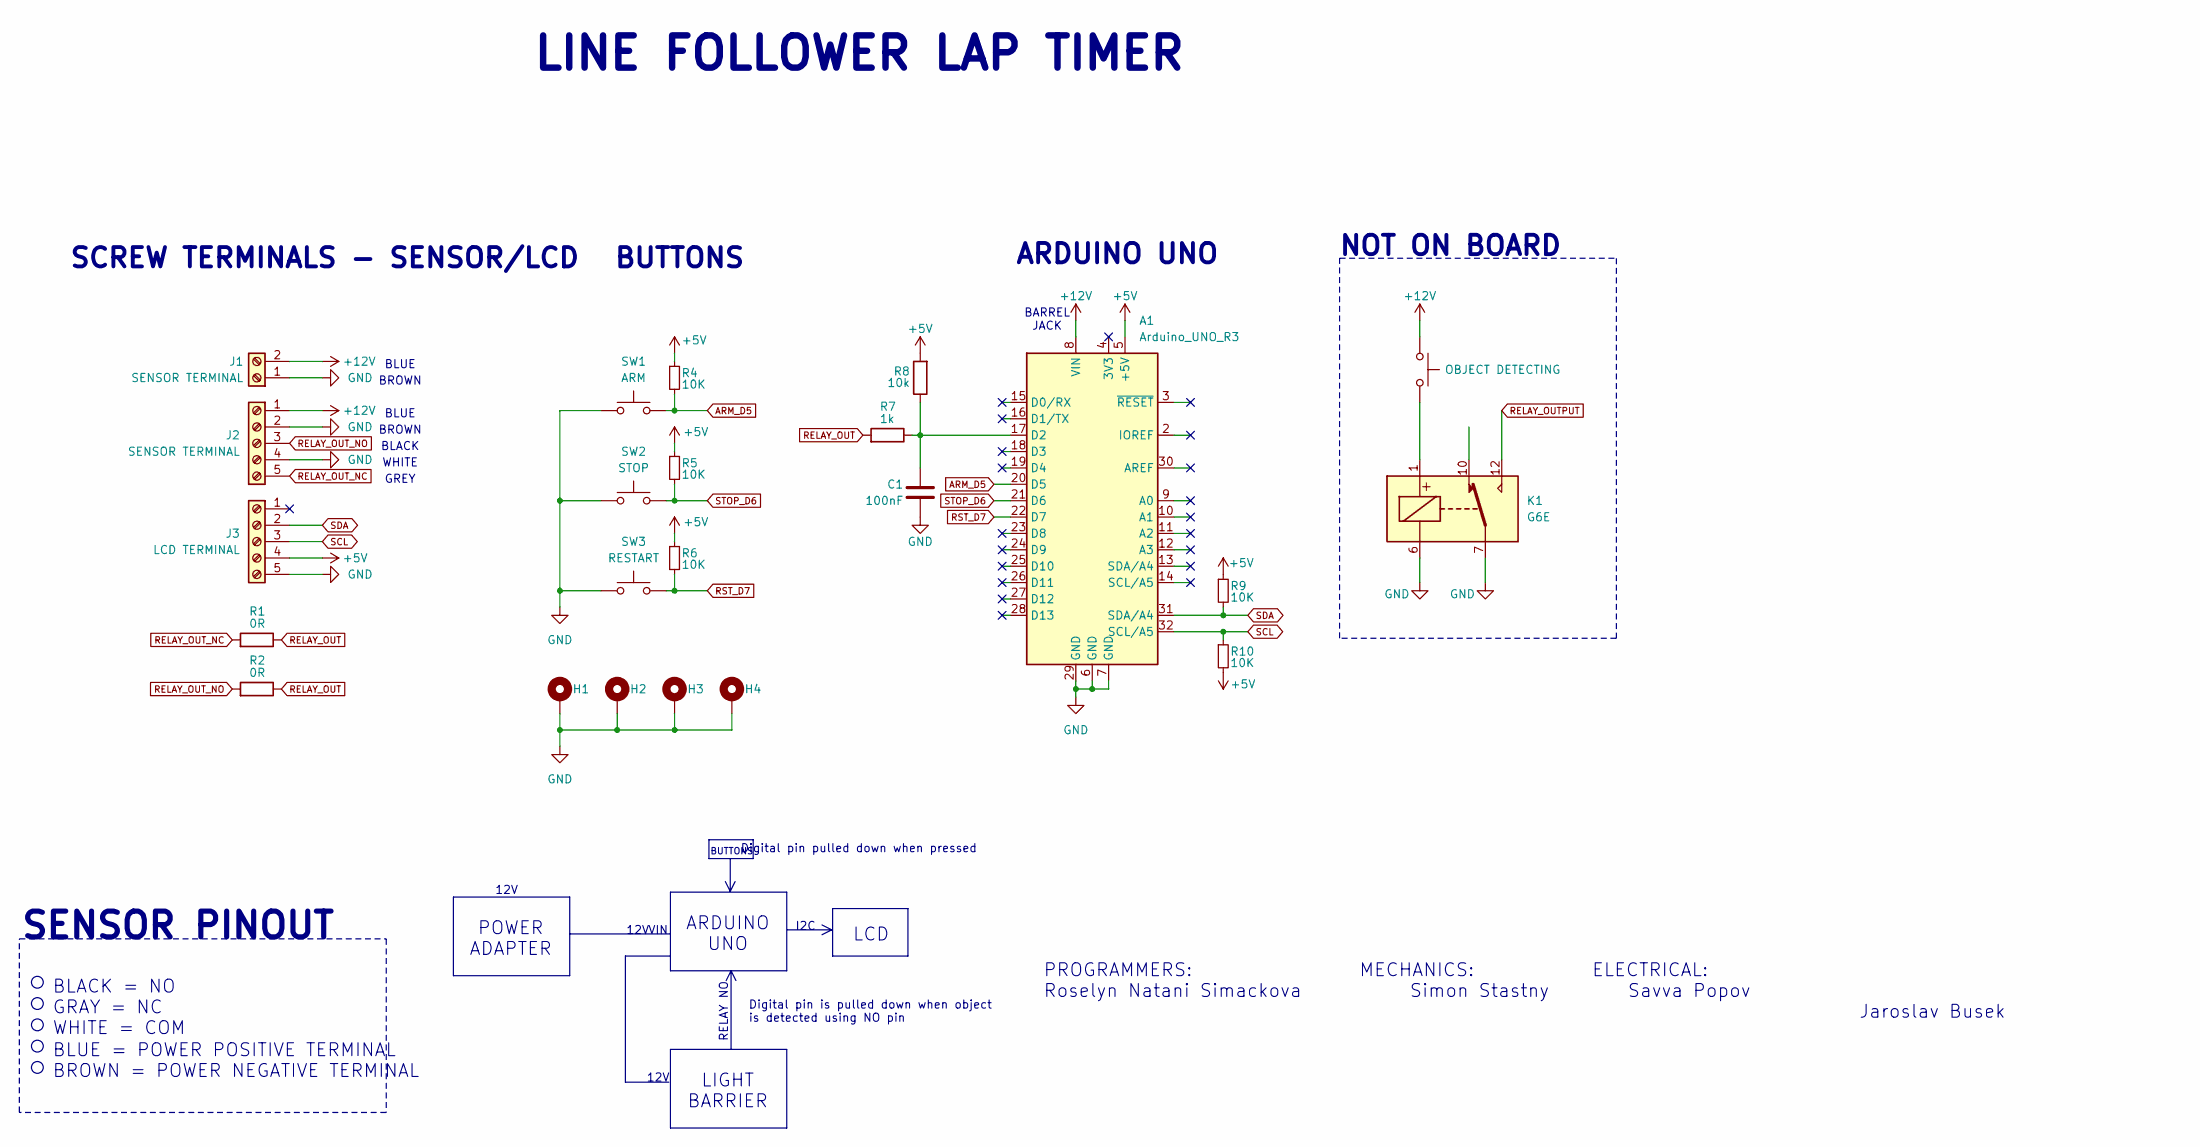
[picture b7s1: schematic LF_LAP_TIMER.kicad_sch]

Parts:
A1: Arduino_UNO_R3
C1: 100nF; C_Disc_D6.0mm_W2.5mm_P5.00mm
H1, H2, H3, H4: MountingHole_Pad; MountingHole_3.2mm_M3_Pad
J1: SENSOR TERMINAL; TerminalBlock_MaiXu_MX126-5.0-02P_1x02_P5.00mm
J2: SENSOR TERMINAL; TerminalBlock_MaiXu_MX126-5.0-05P_1x05_P5.00mm
J3: LCD TERMINAL; TerminalBlock_MaiXu_MX126-5.0-05P_1x05_P5.00mm
K1: G6E
R1, R2: 0R; R_Axial_DIN0207_L6.3mm_D2.5mm_P10.16mm_Horizontal
R4, R5, R6, R9, R10: 10K; R_Axial_DIN0207_L6.3mm_D2.5mm_P10.16mm_Horizontal
R7: 1k; R_Axial_DIN0207_L6.3mm_D2.5mm_P10.16mm_Horizontal
R8: 10k; R_Axial_DIN0207_L6.3mm_D2.5mm_P10.16mm_Horizontal
SW1: ARM; TerminalBlock_MaiXu_MX126-5.0-02P_1x02_P5.00mm
SW2: STOP; TerminalBlock_MaiXu_MX126-5.0-02P_1x02_P5.00mm
SW3: RESTART; TerminalBlock_MaiXu_MX126-5.0-02P_1x02_P5.00mm
SW4: OBJECT DETECTING

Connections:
+5V: A1.5 (+5V), J3.4, R4.1, R5.1, R6.1, R8.2, R9.1, R10.2
+12V: A1.8 (VIN), J1.2, J2.1, SW4.1
ARM_D5: A1.20 (D5), R4.2, SW1.2
GND: A1.6 (GND), A1.7 (GND), A1.29 (GND), C1.2, H1.1, H2.1, H3.1, H4.1, J1.1, J2.2, J2.4, J3.5, K1.6, K1.7, SW1.1, SW2.1, SW3.1
unnamed: A1.17 (D2), C1.1, R7.1, R8.1
unnamed: K1.1, SW4.2
RELAY_OUT: R1.1, R2.1, R7.2
RELAY_OUT_NC: J2.5, R1.2
RELAY_OUT_NO: J2.3, R2.2
RST_D7: A1.22 (D7), R6.2, SW3.2
SCL: A1.32 (SCL/A5), J3.3, R10.1
SDA: A1.31 (SDA/A4), J3.2, R9.2
STOP_D6: A1.21 (D6), R5.2, SW2.2

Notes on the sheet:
BLUE = POWER POSITIVE TERMINAL BROWN = POWER NEGATIVE TERMINAL
ARDUINO UNO
BROWN
BUTTONS
12V
SCREW TERMINALS - SENSOR/LCD
VIN
I2C
SENSOR PINOUT
BARREL JACK
RELAY NO
BLUE
WHITE
LIGHT BARRIER
BLACK
GREY
ARDUINO UNO
LINE FOLLOWER LAP TIMER
LCD
BLACK = NO GRAY = NC WHITE = COM
POWER ADAPTER
NOT ON BOARD
Digital pin pulled down when pressed
PROGRAMMERS: MECHANICS: ELECTRICAL: Roselyn Natani Simackova Simon Stastny Savva Popov Jaroslav Busek
Digital pin is pulled down when object is detected using NO pin

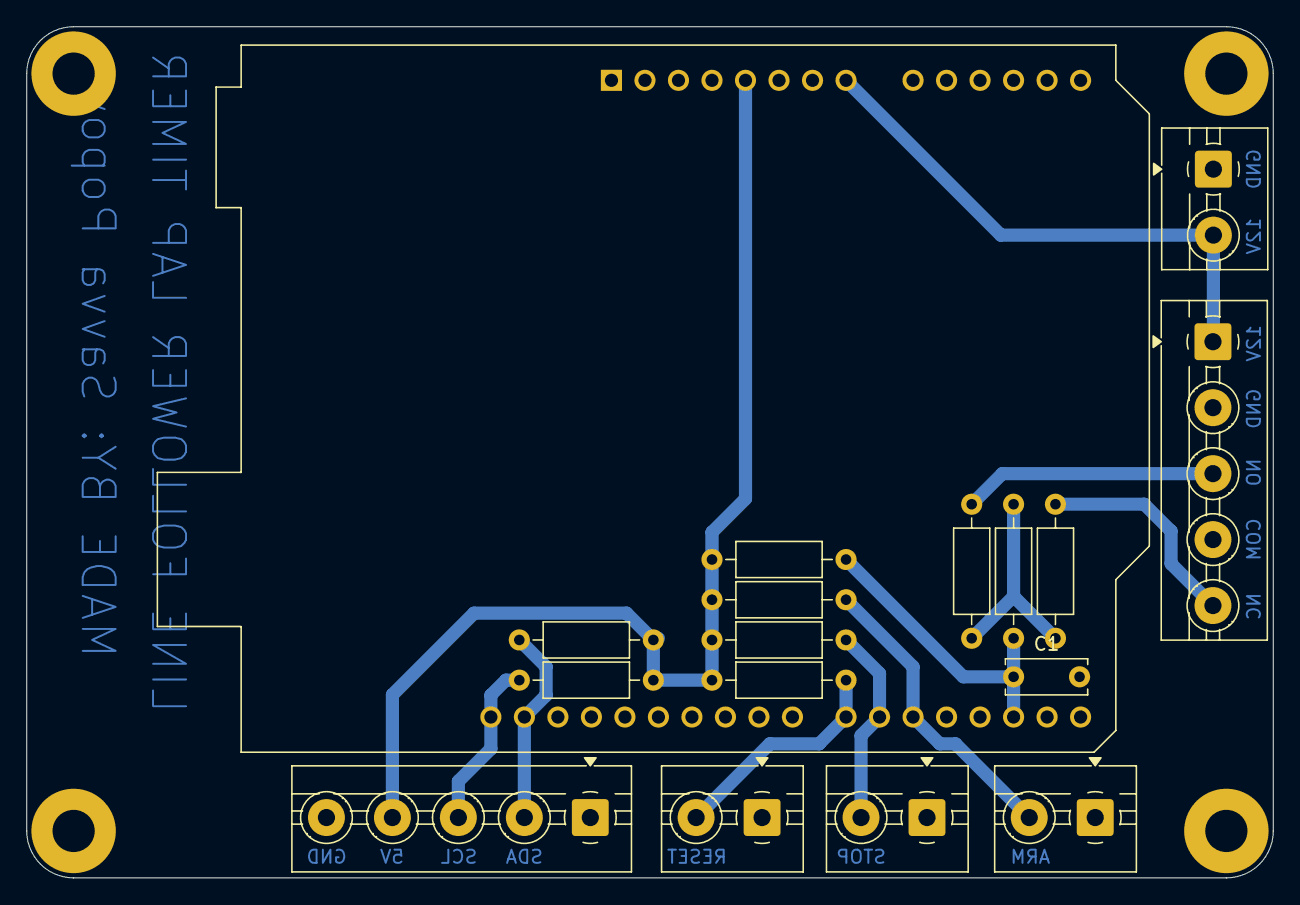
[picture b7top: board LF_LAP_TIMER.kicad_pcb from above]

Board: 2 copper layers, 94.5 x 64.5 mm, 21 parts (0 on the bottom side), 12 nets.
